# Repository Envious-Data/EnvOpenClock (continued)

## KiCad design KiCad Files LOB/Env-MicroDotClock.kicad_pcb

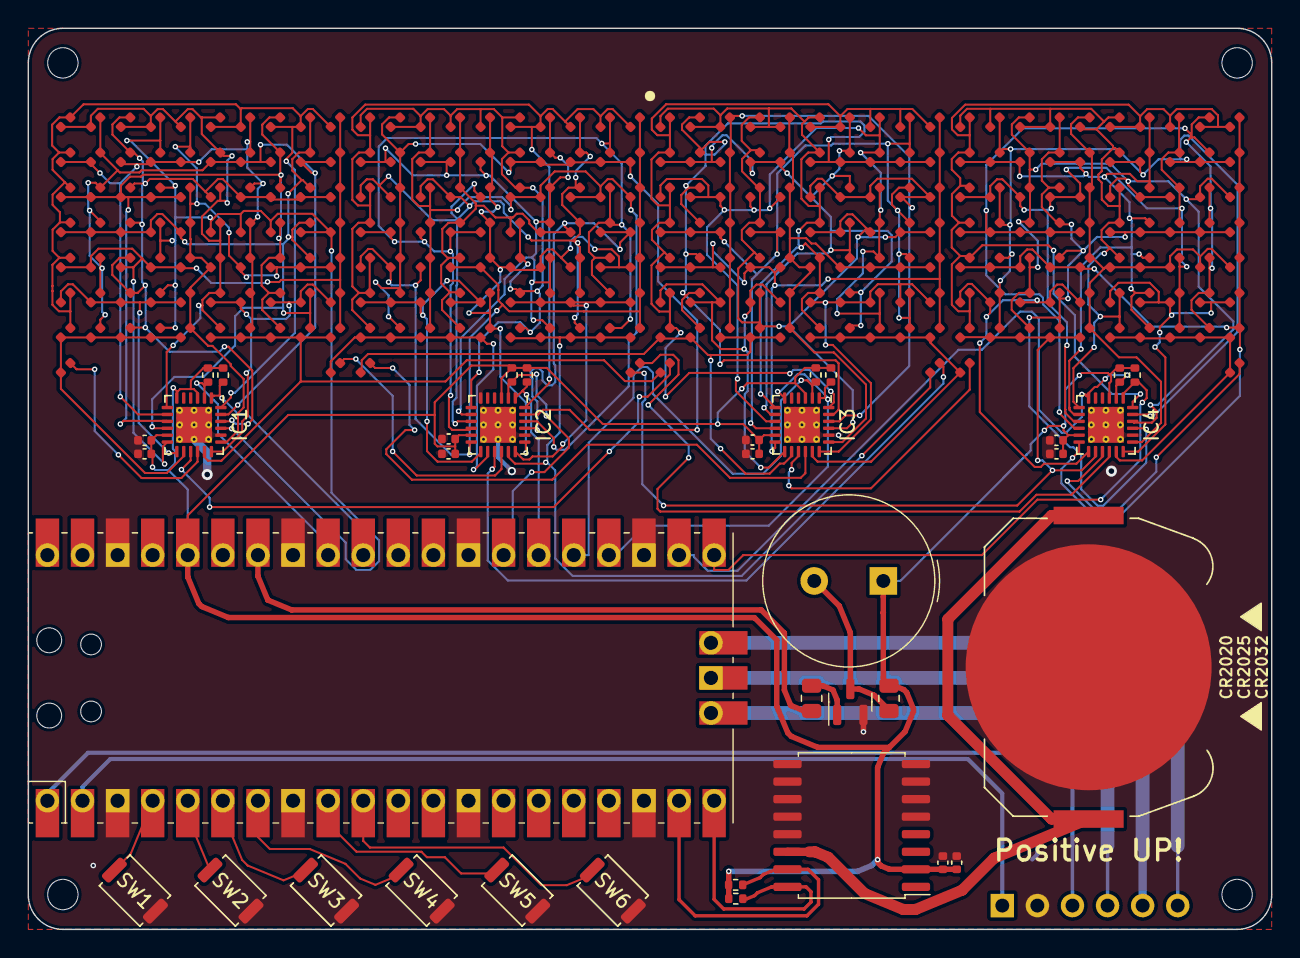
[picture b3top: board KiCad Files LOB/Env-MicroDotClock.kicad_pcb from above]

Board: 2 copper layers, 90.0 x 65.2 mm, 330 parts (1 on the bottom side), 91 nets.

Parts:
BT1: Keystone 3034; BatteryHolder_Keystone_3034_1x20mm
BZ1: Buzzer 12.2Mm; Buzzer_TDK_PS1240P02BT_D12.2mm_H6.5mm
C1, C3, C5, C7, C9: 0402 0.1uF; C_0402_1005Metric
C2, C4, C6, C8, C10: 0402 1uF; C_0402_1005Metric
D2, D3, D4, D5, D6, D7, D8, D9, D10, D11, D12, D13, D14, D15, D16, D17, D18, D19, D20, D21, D22, D23, D24, D25, D26, D27, D28, D29, D30, D31, D32, D33, D34, D35, D36, D38, D39, D40, D41, D42, D43, D44, D45, D46, D47, D48, D49, D50, D51, D52, D53, D54, D55, D56, D57, D58, D59, D60, D61, D62, D63, D64, D65, D66, D67, D68, D69, D70, D71, D72, D74, D75, D76, D77, D78, D79, D80, D81, D82, D83, D84, D85, D86, D87, D88, D89, D90, D91, D92, D93, D94, D95, D96, D97, D98, D99, D100, D101, D102, D103, D104, D105, D106, D107, D108, D110, D111, D112, D113, D114, D115, D116, D117, D118, D119, D120, D121, D122, D123, D124, D125, D126, D127, D128, D129, D130, D131, D132, D133, D134, D135, D136, D137, D138, D139, D140, D141, D142, D143, D144, D146, D147, D148, D149, D150, D151, D152, D153, D154, D155, D156, D157, D158, D159, D160, D161, D162, D163, D164, D165, D166, D167, D168, D169, D170, D171, D172, D173, D174, D175, D176, D177, D178, D179, D180, D182, D183, D184, D185, D186, D187, D188, D189, D190, D191, D192, D193, D194, D195, D196, D197, D198, D199, D200, D201, D202, D203, D204, D205, D206, D207, D208, D209, D210, D211, D212, D213, D214, D215, D216, D218, D219, D220, D221, D222, D223, D224, D225, D226, D227, D228, D229, D230, D231, D232, D233, D234, D235, D236, D237, D238, D239, D240, D241, D242, D243, D244, D245, D246, D247, D248, D249, D250, D251, D252, D254, D255, D256, D257, D258, D259, D260, D261, D262, D263, D264, D265, D266, D267, D268, D269, D270, D271, D272, D273, D274, D275, D276, D277, D278, D279, D280, D281, D282, D283, D284, D285, D286, D287, D288: LED; LED_0402_1005Metric
DI1, DI2, DI3, DI4, DI5, DI6, DI7, DI8: LED; LED_0402_1005Metric
H1, H2, H3, H4: MountingHole; MountingHole_2.2mm_M2
IC1, IC2, IC3, IC4: IS31FL3730-QFLS2-TR; QFN-24-1EP_4x4mm_P0.5mm_EP2.6x2.6mm_ThermalVias
J1: Conn_01x06_Pin; PinHeader_1x06_P2.54mm_Vertical
Q1: 2SC1815; SOT-23
R1, R2, R5, R6, R7, R8, R9, R10, R11, R12: 0402 10K; R_0402_1005Metric
R3, R4: 0805 1K; R_0805_2012Metric
SW1, SW2, SW3, SW4, SW5, SW6: SW_SPST; SW_Push_SPST_NO_Alps_SKRK
U1: Raspberry Pi Pico; RPi_Pico_SMD_TH
U3: DS3231M; SOIC-16W_7.5x10.3mm_P1.27mm

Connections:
+3V3: BZ1.1 (-), C1.1, C2.1, C3.1, C4.1, C5.1, C6.1, C7.1, C8.1, C9.1, C10.1, IC1.3 (SDB), IC1.6 (AD), IC1.11 (VCC), IC2.3 (SDB), IC2.11 (VCC), IC3.3 (SDB), IC3.11 (VCC), IC4.3 (SDB), IC4.11 (VCC), R1.1, R2.1, R3.1, R5.1, R6.1, R7.1, R8.1, R9.1, R10.1, R11.1, R12.1, U1.36 (3V3), U3.2 (VCC)
Buzzer GPIO: R4.1, U1.34 (GPIO28_ADC2)
DEBUG-GND: J1.5, U1.42 (GND)
GND: BT1.2 (-), C1.2, C2.2, C3.2, C4.2, C5.2, C6.2, C7.2, C8.2, C9.2, C10.2, IC1.20 (GND_1), IC1.25 (GND_2), IC2.6 (AD), IC2.20 (GND_1), IC2.25 (GND_2), IC3.20 (GND_1), IC3.25 (GND_2), IC4.20 (GND_1), IC4.25 (GND_2), J1.2, Q1.2 (E), SW1.2 (B), SW2.2 (B), SW3.2 (B), SW4.2 (B), SW5.2 (B), SW6.2 (B), U1.3 (GND), U1.8 (GND), U1.13 (GND), U1.18 (GND), U1.23 (GND), U1.28 (GND), U1.33 (AGND), U1.38 (GND), U3.5 (GND), U3.6 (GND), U3.7 (GND), U3.8 (GND), U3.9 (GND), U3.10 (GND), U3.11 (GND), U3.12 (GND), U3.13 (GND)
GPIO2: SW1.1 (A), U1.4 (GPIO2)
GPIO3: SW2.1 (A), U1.5 (GPIO3)
GPIO4: SW3.1 (A), U1.6 (GPIO4)
GPIO5: SW4.1 (A), U1.7 (GPIO5)
GPIO6: SW5.1 (A), U1.9 (GPIO6)
GPIO7: SW6.1 (A), U1.10 (GPIO7)
I2C1_SCL: IC1.2 (SCL), R10.2, U1.32 (GPIO27_ADC1)
I2C1_SDA: IC1.1 (SDA), R9.2, U1.31 (GPIO26_ADC0)
I2C2_SCL: IC2.2 (SCL), R12.2, U1.27 (GPIO21)
I2C2_SDA: IC2.1 (SDA), R11.2, U1.26 (GPIO20)
I2C3_SCL: IC3.2 (SCL), R8.2, U1.25 (GPIO19)
I2C3_SDA: IC3.1 (SDA), IC3.6 (AD), R7.2, U1.24 (GPIO18)
I2C4_SCL: IC4.2 (SCL), IC4.6 (AD), R6.2, U1.22 (GPIO17)
I2C4_SDA: IC4.1 (SDA), R5.2, U1.21 (GPIO16)
IC1C1: D2.2 (A), D3.2 (A), D4.2 (A), D5.2 (A), D6.2 (A), D7.2 (A), D8.2 (A), D146.1 (K), D153.1 (K), D160.1 (K), D167.1 (K), D174.1 (K), IC1.24 (C1)
IC1C2: D9.2 (A), D10.2 (A), D11.2 (A), D12.2 (A), D13.2 (A), D14.2 (A), D15.2 (A), D147.1 (K), D154.1 (K), D161.1 (K), D168.1 (K), D175.1 (K), IC1.23 (C2)
IC1C3: D16.2 (A), D17.2 (A), D18.2 (A), D19.2 (A), D20.2 (A), D21.2 (A), D22.2 (A), D148.1 (K), D155.1 (K), D162.1 (K), D169.1 (K), D176.1 (K), IC1.22 (C3)
IC1C4: D23.2 (A), D24.2 (A), D25.2 (A), D26.2 (A), D27.2 (A), D28.2 (A), D29.2 (A), D149.1 (K), D156.1 (K), D163.1 (K), D170.1 (K), D177.1 (K), IC1.21 (C4)
IC1C5: D30.2 (A), D31.2 (A), D32.2 (A), D33.2 (A), D34.2 (A), D35.2 (A), D36.2 (A), D150.1 (K), D157.1 (K), D164.1 (K), D171.1 (K), D178.1 (K), IC1.19 (C5)
IC1C6: D151.1 (K), D158.1 (K), D165.1 (K), D172.1 (K), D179.1 (K), IC1.18 (C6)
IC1C7: D152.1 (K), D159.1 (K), D166.1 (K), D173.1 (K), D180.1 (K), DI5.1 (K), IC1.17 (C7)
IC1C8: DI1.2 (A), IC1.16 (C8)
IC1R1: D2.1 (K), D9.1 (K), D16.1 (K), D23.1 (K), D30.1 (K), D146.2 (A), D147.2 (A), D148.2 (A), D149.2 (A), D150.2 (A), D151.2 (A), D152.2 (A), IC1.7 (R1)
IC1R2: D3.1 (K), D10.1 (K), D17.1 (K), D24.1 (K), D31.1 (K), D153.2 (A), D154.2 (A), D155.2 (A), D156.2 (A), D157.2 (A), D158.2 (A), D159.2 (A), IC1.8 (R2)
IC1R3: D4.1 (K), D11.1 (K), D18.1 (K), D25.1 (K), D32.1 (K), D160.2 (A), D161.2 (A), D162.2 (A), D163.2 (A), D164.2 (A), D165.2 (A), D166.2 (A), IC1.9 (R3)
IC1R4: D5.1 (K), D12.1 (K), D19.1 (K), D26.1 (K), D33.1 (K), D167.2 (A), D168.2 (A), D169.2 (A), D170.2 (A), D171.2 (A), D172.2 (A), D173.2 (A), IC1.10 (R4)
IC1R5: D6.1 (K), D13.1 (K), D20.1 (K), D27.1 (K), D34.1 (K), D174.2 (A), D175.2 (A), D176.2 (A), D177.2 (A), D178.2 (A), D179.2 (A), D180.2 (A), IC1.12 (R5)
IC1R6: D7.1 (K), D14.1 (K), D21.1 (K), D28.1 (K), D35.1 (K), IC1.13 (R6/C11)
IC1R7: D8.1 (K), D15.1 (K), D22.1 (K), D29.1 (K), D36.1 (K), DI1.1 (K), IC1.14 (R7/C10)
IC1R8: DI5.2 (A), IC1.15 (R8/C9)
IC2C1: D38.2 (A), D39.2 (A), D40.2 (A), D41.2 (A), D42.2 (A), D43.2 (A), D44.2 (A), D182.1 (K), D189.1 (K), D196.1 (K), D203.1 (K), D210.1 (K), IC2.24 (C1)
IC2C2: D45.2 (A), D46.2 (A), D47.2 (A), D48.2 (A), D49.2 (A), D50.2 (A), D51.2 (A), D183.1 (K), D190.1 (K), D197.1 (K), D204.1 (K), D211.1 (K), IC2.23 (C2)
IC2C3: D52.2 (A), D53.2 (A), D54.2 (A), D55.2 (A), D56.2 (A), D57.2 (A), D58.2 (A), D184.1 (K), D191.1 (K), D198.1 (K), D205.1 (K), D212.1 (K), IC2.22 (C3)
IC2C4: D59.2 (A), D60.2 (A), D61.2 (A), D62.2 (A), D63.2 (A), D64.2 (A), D65.2 (A), D185.1 (K), D192.1 (K), D199.1 (K), D206.1 (K), D213.1 (K), IC2.21 (C4)
IC2C5: D66.2 (A), D67.2 (A), D68.2 (A), D69.2 (A), D70.2 (A), D71.2 (A), D72.2 (A), D186.1 (K), D193.1 (K), D200.1 (K), D207.1 (K), D214.1 (K), IC2.19 (C5)
IC2C6: D187.1 (K), D194.1 (K), D201.1 (K), D208.1 (K), D215.1 (K), IC2.18 (C6)
IC2C7: D188.1 (K), D195.1 (K), D202.1 (K), D209.1 (K), D216.1 (K), DI6.1 (K), IC2.17 (C7)
IC2C8: DI2.2 (A), IC2.16 (C8)
IC2R1: D38.1 (K), D45.1 (K), D52.1 (K), D59.1 (K), D66.1 (K), D182.2 (A), D183.2 (A), D184.2 (A), D185.2 (A), D186.2 (A), D187.2 (A), D188.2 (A), IC2.7 (R1)
IC2R2: D39.1 (K), D46.1 (K), D53.1 (K), D60.1 (K), D67.1 (K), D189.2 (A), D190.2 (A), D191.2 (A), D192.2 (A), D193.2 (A), D194.2 (A), D195.2 (A), IC2.8 (R2)
IC2R3: D40.1 (K), D47.1 (K), D54.1 (K), D61.1 (K), D68.1 (K), D196.2 (A), D197.2 (A), D198.2 (A), D199.2 (A), D200.2 (A), D201.2 (A), D202.2 (A), IC2.9 (R3)
IC2R4: D41.1 (K), D48.1 (K), D55.1 (K), D62.1 (K), D69.1 (K), D203.2 (A), D204.2 (A), D205.2 (A), D206.2 (A), D207.2 (A), D208.2 (A), D209.2 (A), IC2.10 (R4)
IC2R5: D42.1 (K), D49.1 (K), D56.1 (K), D63.1 (K), D70.1 (K), D210.2 (A), D211.2 (A), D212.2 (A), D213.2 (A), D214.2 (A), D215.2 (A), D216.2 (A), IC2.12 (R5)
IC2R6: D43.1 (K), D50.1 (K), D57.1 (K), D64.1 (K), D71.1 (K), IC2.13 (R6/C11)
IC2R7: D44.1 (K), D51.1 (K), D58.1 (K), D65.1 (K), D72.1 (K), DI2.1 (K), IC2.14 (R7/C10)
IC2R8: DI6.2 (A), IC2.15 (R8/C9)
IC3C1: D74.2 (A), D75.2 (A), D76.2 (A), D77.2 (A), D78.2 (A), D79.2 (A), D80.2 (A), D218.1 (K), D225.1 (K), D232.1 (K), D239.1 (K), D246.1 (K), IC3.24 (C1)
IC3C2: D81.2 (A), D82.2 (A), D83.2 (A), D84.2 (A), D85.2 (A), D86.2 (A), D87.2 (A), D219.1 (K), D226.1 (K), D233.1 (K), D240.1 (K), D247.1 (K), IC3.23 (C2)
IC3C3: D88.2 (A), D89.2 (A), D90.2 (A), D91.2 (A), D92.2 (A), D93.2 (A), D94.2 (A), D220.1 (K), D227.1 (K), D234.1 (K), D241.1 (K), D248.1 (K), IC3.22 (C3)
IC3C4: D95.2 (A), D96.2 (A), D97.2 (A), D98.2 (A), D99.2 (A), D100.2 (A), D101.2 (A), D221.1 (K), D228.1 (K), D235.1 (K), D242.1 (K), D249.1 (K), IC3.21 (C4)
IC3C5: D102.2 (A), D103.2 (A), D104.2 (A), D105.2 (A), D106.2 (A), D107.2 (A), D108.2 (A), D222.1 (K), D229.1 (K), D236.1 (K), D243.1 (K), D250.1 (K), IC3.19 (C5)
IC3C6: D223.1 (K), D230.1 (K), D237.1 (K), D244.1 (K), D251.1 (K), IC3.18 (C6)
IC3C7: D224.1 (K), D231.1 (K), D238.1 (K), D245.1 (K), D252.1 (K), DI7.1 (K), IC3.17 (C7)
IC3C8: DI3.2 (A), IC3.16 (C8)
IC3R1: D74.1 (K), D81.1 (K), D88.1 (K), D95.1 (K), D102.1 (K), D218.2 (A), D219.2 (A), D220.2 (A), D221.2 (A), D222.2 (A), D223.2 (A), D224.2 (A), IC3.7 (R1)
IC3R2: D75.1 (K), D82.1 (K), D89.1 (K), D96.1 (K), D103.1 (K), D225.2 (A), D226.2 (A), D227.2 (A), D228.2 (A), D229.2 (A), D230.2 (A), D231.2 (A), IC3.8 (R2)
IC3R3: D76.1 (K), D83.1 (K), D90.1 (K), D97.1 (K), D104.1 (K), D232.2 (A), D233.2 (A), D234.2 (A), D235.2 (A), D236.2 (A), D237.2 (A), D238.2 (A), IC3.9 (R3)
IC3R4: D77.1 (K), D84.1 (K), D91.1 (K), D98.1 (K), D105.1 (K), D239.2 (A), D240.2 (A), D241.2 (A), D242.2 (A), D243.2 (A), D244.2 (A), D245.2 (A), IC3.10 (R4)
IC3R5: D78.1 (K), D85.1 (K), D92.1 (K), D99.1 (K), D106.1 (K), D246.2 (A), D247.2 (A), D248.2 (A), D249.2 (A), D250.2 (A), D251.2 (A), D252.2 (A), IC3.12 (R5)
IC3R6: D79.1 (K), D86.1 (K), D93.1 (K), D100.1 (K), D107.1 (K), IC3.13 (R6/C11)
IC3R7: D80.1 (K), D87.1 (K), D94.1 (K), D101.1 (K), D108.1 (K), DI3.1 (K), IC3.14 (R7/C10)
IC3R8: DI7.2 (A), IC3.15 (R8/C9)
IC4C1: D110.2 (A), D111.2 (A), D112.2 (A), D113.2 (A), D114.2 (A), D115.2 (A), D116.2 (A), D254.1 (K), D261.1 (K), D268.1 (K), D275.1 (K), D282.1 (K), IC4.24 (C1)
IC4C2: D117.2 (A), D118.2 (A), D119.2 (A), D120.2 (A), D121.2 (A), D122.2 (A), D123.2 (A), D255.1 (K), D262.1 (K), D269.1 (K), D276.1 (K), D283.1 (K), IC4.23 (C2)
IC4C3: D124.2 (A), D125.2 (A), D126.2 (A), D127.2 (A), D128.2 (A), D129.2 (A), D130.2 (A), D256.1 (K), D263.1 (K), D270.1 (K), D277.1 (K), D284.1 (K), IC4.22 (C3)
IC4C4: D131.2 (A), D132.2 (A), D133.2 (A), D134.2 (A), D135.2 (A), D136.2 (A), D137.2 (A), D257.1 (K), D264.1 (K), D271.1 (K), D278.1 (K), D285.1 (K), IC4.21 (C4)
IC4C5: D138.2 (A), D139.2 (A), D140.2 (A), D141.2 (A), D142.2 (A), D143.2 (A), D144.2 (A), D258.1 (K), D265.1 (K), D272.1 (K), D279.1 (K), D286.1 (K), IC4.19 (C5)
IC4C6: D259.1 (K), D266.1 (K), D273.1 (K), D280.1 (K), D287.1 (K), IC4.18 (C6)
IC4C7: D260.1 (K), D267.1 (K), D274.1 (K), D281.1 (K), D288.1 (K), DI8.1 (K), IC4.17 (C7)
IC4C8: DI4.2 (A), IC4.16 (C8)
IC4R1: D110.1 (K), D117.1 (K), D124.1 (K), D131.1 (K), D138.1 (K), D254.2 (A), D255.2 (A), D256.2 (A), D257.2 (A), D258.2 (A), D259.2 (A), D260.2 (A), IC4.7 (R1)
IC4R2: D111.1 (K), D118.1 (K), D125.1 (K), D132.1 (K), D139.1 (K), D261.2 (A), D262.2 (A), D263.2 (A), D264.2 (A), D265.2 (A), D266.2 (A), D267.2 (A), IC4.8 (R2)
IC4R3: D112.1 (K), D119.1 (K), D126.1 (K), D133.1 (K), D140.1 (K), D268.2 (A), D269.2 (A), D270.2 (A), D271.2 (A), D272.2 (A), D273.2 (A), D274.2 (A), IC4.9 (R3)
IC4R4: D113.1 (K), D120.1 (K), D127.1 (K), D134.1 (K), D141.1 (K), D275.2 (A), D276.2 (A), D277.2 (A), D278.2 (A), D279.2 (A), D280.2 (A), D281.2 (A), IC4.10 (R4)
IC4R5: D114.1 (K), D121.1 (K), D128.1 (K), D135.1 (K), D142.1 (K), D282.2 (A), D283.2 (A), D284.2 (A), D285.2 (A), D286.2 (A), D287.2 (A), D288.2 (A), IC4.12 (R5)
IC4R6: D115.1 (K), D122.1 (K), D129.1 (K), D136.1 (K), D143.1 (K), IC4.13 (R6/C11)
IC4R7: D116.1 (K), D123.1 (K), D130.1 (K), D137.1 (K), D144.1 (K), DI4.1 (K), IC4.14 (R7/C10)
IC4R8: DI8.2 (A), IC4.15 (R8/C9)
unnamed: BT1.1 (+), U3.14 (VBAT)
unnamed: BZ1.2 (+), Q1.3 (C), R3.2
unnamed: Q1.1 (B), R4.2
RTC_SCL: R1.2, U1.20 (GPIO15), U3.16 (SCL)
RTC_SDA: R2.2, U1.19 (GPIO14), U3.15 (SDA)
RX: J1.1, U1.2 (GPIO1)
SWCLK: J1.4, U1.41 (SWCLK)
SWDIO: J1.6, U1.43 (SWDIO)
TX: J1.3, U1.1 (GPIO0)

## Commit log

2023-06-05 First commit.
2023-06-05 generated production files for JLCPCB.
2023-06-05 small changes and fixes, among other adjustments.
2023-06-06 some fixes and adjustments.
2023-06-07 Moved LTP305s up and the matrix ICs below the LTP305s
2023-06-07 updated production files
2023-06-10 added dip switch for summer time adjustment
2023-06-10 swapped dipswitch for smaller
2023-07-05 dont recall what I changed, probably cleaned some bits up before generating gerber
2023-07-11 updated to reflect current vision.
2023-07-20 made values more descriptive for SMTA
2023-08-19 Fixed pullups, they ran to 5V instead of 3.3V meaning they would fry the MCU pins eventually
2023-08-20 pushing for cat
2023-08-20 lookee here
2023-08-20 Added some c
2023-08-21 for jum
2023-08-21 rotated the battery holder so the battery inserts from the side.
2023-08-21 updated battery Silkscreen
2023-08-21 updated readme with more information
2023-08-21 added timouts
2023-08-21 roll back push DO NOT USE
2023-08-21 Revert "added timouts"
    This reverts commit 298f98d779afaf4c9fa04b243778e5b8981776b4.
2023-08-23 adjusted silkscreen again
2023-08-23 Optimised Update Display
2023-08-23 Updated to use i2c_write_blocking_until
2023-08-23 Updated to use i2c_write_blocking_until in rtc.c
2023-08-23 Updated to use i2c_*_timeout_us
2023-08-23 testing chip 1
2023-08-23 testing chip 2
2023-08-23 testing chip 3 - failed
2023-08-24 Added comments to display driver
2023-08-26 swapped 5V for 3V3 as per information on the datasheet
2023-08-26 clean the build folder for anyone else testing this
2023-08-26 moved all i2c devices to dedicated gpio pairs, added individual pullups, ensured everything is 3.3V VCC or logic level 3V3 tied
2023-08-26 changes toward a V2, replaced battery holder with larger one, moved rtc leftward to make space for larger battery.
2023-08-26 small tweaks + generated production files
2023-08-28 removed all traces for work on future version
2023-08-28 added a simple stand for the clock
2023-08-29 Kicad Verion
2023-08-29 Kicad Verion - Power Traces Alone
2023-08-29 Revert "Kicad Verion - Power Traces Alone"
    This reverts commit 158b1d36a461ef127bb1067e7f7cef4c0585e52c.
2023-08-30 ru version
2023-08-30 aligned and organized components on main variant
2023-08-30 overhauled PCB traces and deleted old production files
2023-09-09 fixed up some issues I saw, general improvements and adjustments to PCB
2023-09-09 made a roundfied version
2023-09-09 rename 1 file
2023-09-09 Added Signatures
2023-09-09 Added debugging headder and sig
2023-09-10 schema push
2023-09-10 prettied up pcb some more and organised schematic
2023-09-10 added more buttons, re-worked some bits and pieces here and there.
2023-09-10 added missing teardrops and fixed a couple overlapped traces
2023-09-11 added leds on board (LOB)
2023-09-11 begin autorouter
2023-09-11 Fully wired V1 LOB
2023-09-11 Polish commit
2023-09-15 Re-worked board to have optional VCC source, rear usb and a few other adjustments
2023-09-18 adjusted a couple traces I Didnt like
2023-09-20 Added ability to set time and show date!
2023-09-21 removed buzzer so I could fit USB port in a better place, allowing for a pimoroni lipo shim to be installed
2023-09-21 cleaned up production files..
2023-10-07 Added Pico On Board
2023-10-08 Added onboard pico
2023-10-08 for cat
2023-10-08 for cat with onboard pico
2023-10-08 Commit for night, progess on onboard RP2040
2023-10-10 sync push
2023-10-10 Finished V1 Placement of onboard pico
2023-10-10 Finished V2 placement and base wireing of RP2040
2023-10-10 fulkly wired v2
2024-04-01 began rework of onboard 2040 pcb
2024-04-01 commit current progress
2024-04-01 finished up and cleaned up PCB, added logos
2024-04-01 generated production files
2024-04-20 added thermal vias, improved gnd connections from IS31FL37s, added thermal vias, added power only usb port on the back.
2024-06-05 swapped LDO for more capable switching regulator.
2024-08-23 added a text note
2024-08-28 added brightness shift
2024-08-28 all changes
2024-08-28 Moved all ICs to one i2c bus, removed SI7021, added i2c level shifters.
2024-09-12 Fixed issues with I2C, added I2C shifter
2024-09-12 corrected couple missing connections
2024-09-12 forgot to fill zone
2024-09-12 removed sockets, added level shifter IC, changed RTC to smaller package, re-did entire board to be more tidy.
2024-09-12 added some silkscreen labels
2024-10-15 corrected schematic file name
2024-11-21 small corrections
2025-03-18 added a sliding animation, still some issues to work out like seperators not showing on startup.
2025-03-18 one very silly fix for missing separators on start-up.
2025-03-18 fixed the semicolon issue, added startup message, added python script to sync time to the clock from your pc.
2025-03-18 sped up animation speed, added reset via serial and attempted to add a watchdog for i2c hang.
2025-03-19 added new animations, changed some code to be less bulky, allowed animation to be set over serial, added python scripts to make life easier.
2025-03-19 supressed errors, added various prints to whats going on.
2025-03-19 added more animations to see which ones I like.
2025-03-19 added a basic debounce as it was easy to skip over animations when pressing the button to cycle them.
2025-03-19 animated the switch between time and date and back.
2025-03-22 got rid of some animations that look too similar to the default slide up.
2025-03-22 changed startup animation to also include separators instead of going to 00:00:00, randomised animation on startup, tried to implement a full display startup animation but couldnt figure it out.
2025-03-28 corrected orientation of various animations, made the date and time mode use the current animation instead of slide up.
2025-03-28 added brightness cycling and override variables for night time.
2025-03-28 forgot to hit save, updated timer callback
